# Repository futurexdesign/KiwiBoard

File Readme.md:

# Kiwiboard 
Control board for the KiwiCleaner watch cleaning machine.  Intended to provide an all-in-one option for the design. 

## Board Goals
- Have a single PCB with connections for the stepper motor, heater, fan, and user interface for ease of wiring. 
- Integrate a Trinamic silent stepper driver to greatly reduce volume. 
- Simplify the user interface for switching between run-modes. 
- Allow cooling fan to run for a timed period after a dry cycle, to allow the heater to safely cool down. 
- Not cost too much more than the original solution, with the understanding that there is greater functionality. 

## Theory of Operation
- Power input is 12V 
- Input is protected by a resettable PolyFuse with rated 10A constant load capacity.  
- Main Microcontroller is a RaspberryPi Pico (RP2040).  
  - This can be either the normal version, or the "header" version.  Can be mounted either way, board contains both the SMD and THT pads. 
- Display a 240x320 Color TFT LCD Connected via SPI
- User interface is controlled via a rotary encoder with pushbutton
- Pico has full control of stepper via SPI connection to the TMC5160 board. 
   - The Integrated Ramp Generator contained within the TMC5160 is utilized to control all motion, allowing very smooth and precise control over basket motion.  
- Pico can enable / disable the drive output via MOTOR_EN (Active Low)
- Pico can activate the Heater by pulling HEATER_CTL High, switching on the relay (3.3v coil).
- Pico can activate the fan by pulling FAN_CTL high, fan current conducted by the TIP120
- 3.3v power provided by a drop in switching powersupply module for simplicity. 
- All power connectors are Phoenix LPT lever connectors.  These support 12awg - 24awg up to a max of 24A.  Can substitute in SPT or any other phoenix connector with the same 5mm pin spacing

An expansion header has been added to support any additional mods people may want. *Example functionality would be a buzzer module to indicate end of cycle.*  Due to the flexability of the microcontroller, we can expose a ton of functionality on 4 pins.  The following IO is available on the expansion connector. 

- 4 independent GPIO pins for input/output 
- 1 hardware i2c bus (i2c1), and 2 GPIO pins (GPI0 and GPIO1)
- 4 pins with a PIO program assigned to them. 

Additionally the expansion header supplys 3.3V and GND connections.

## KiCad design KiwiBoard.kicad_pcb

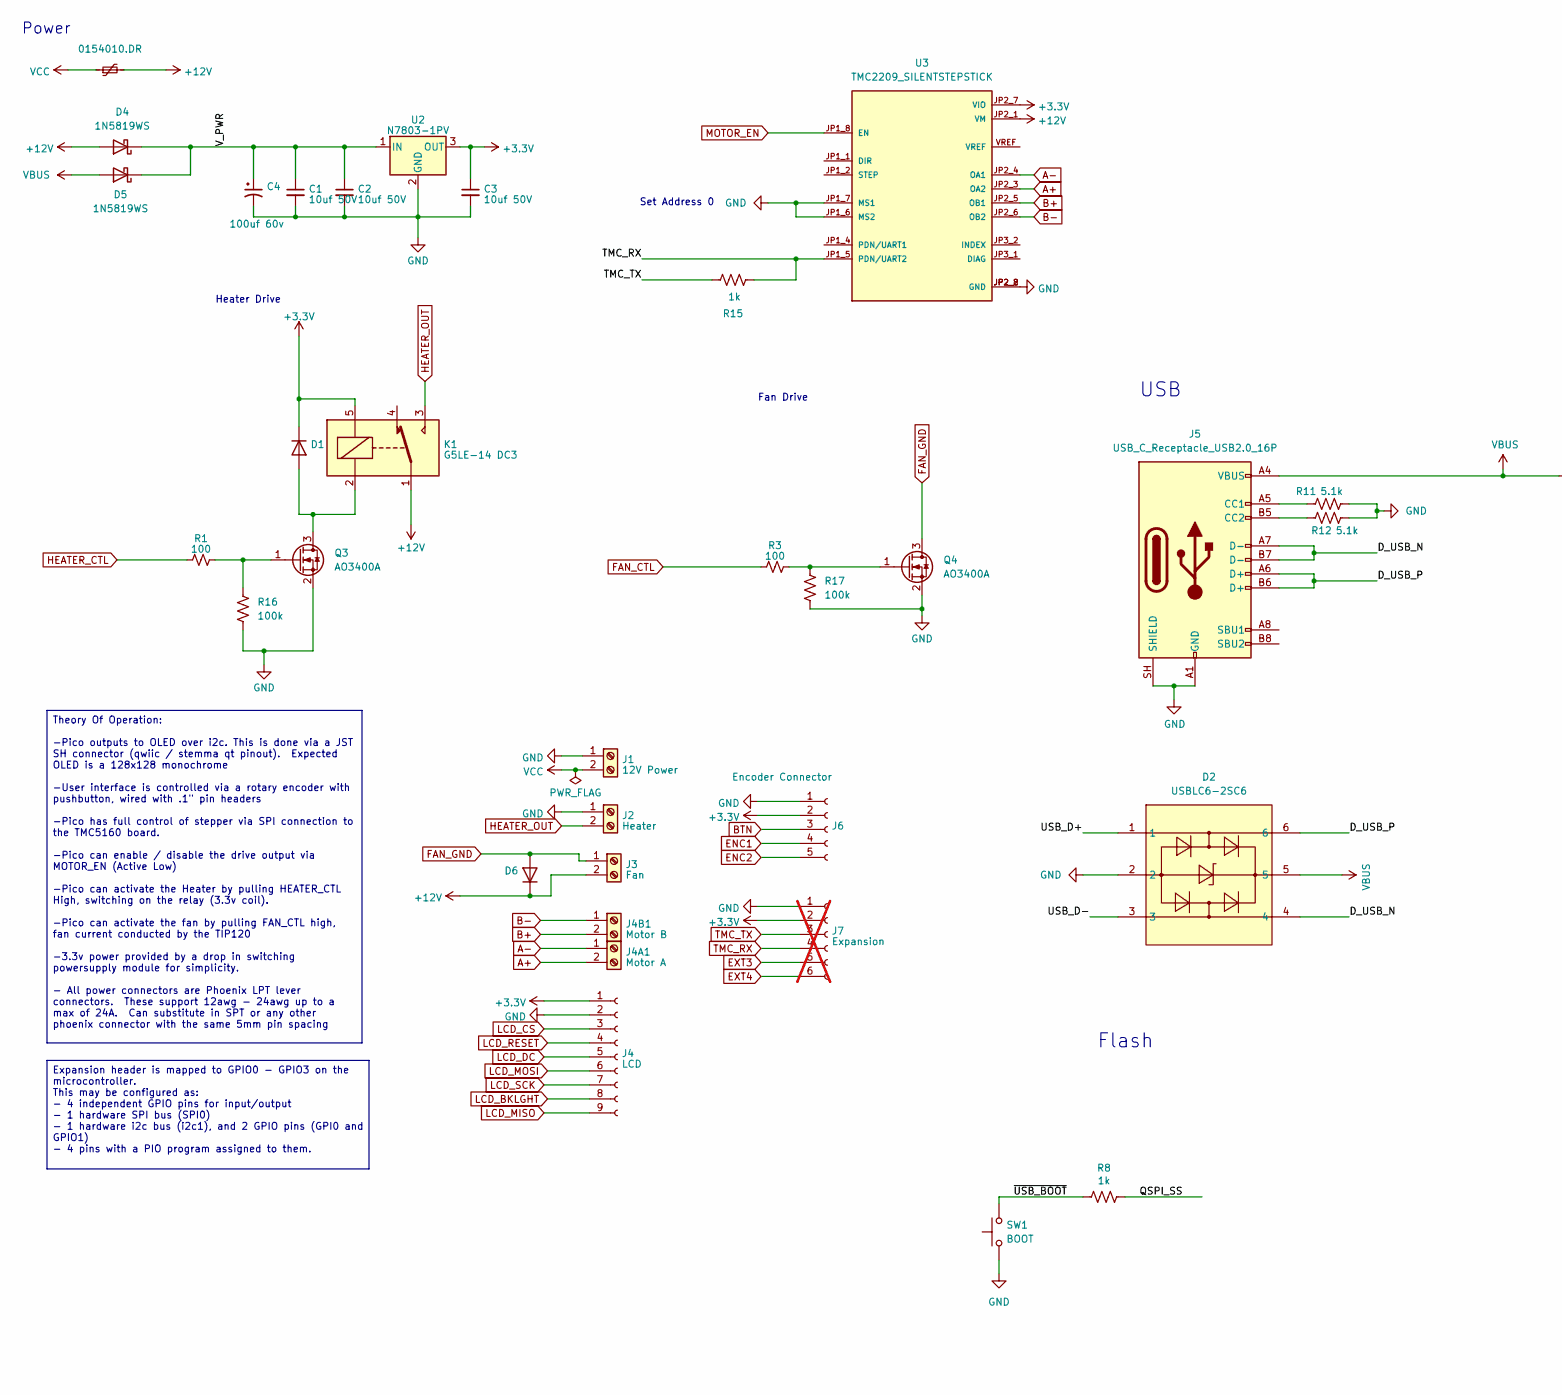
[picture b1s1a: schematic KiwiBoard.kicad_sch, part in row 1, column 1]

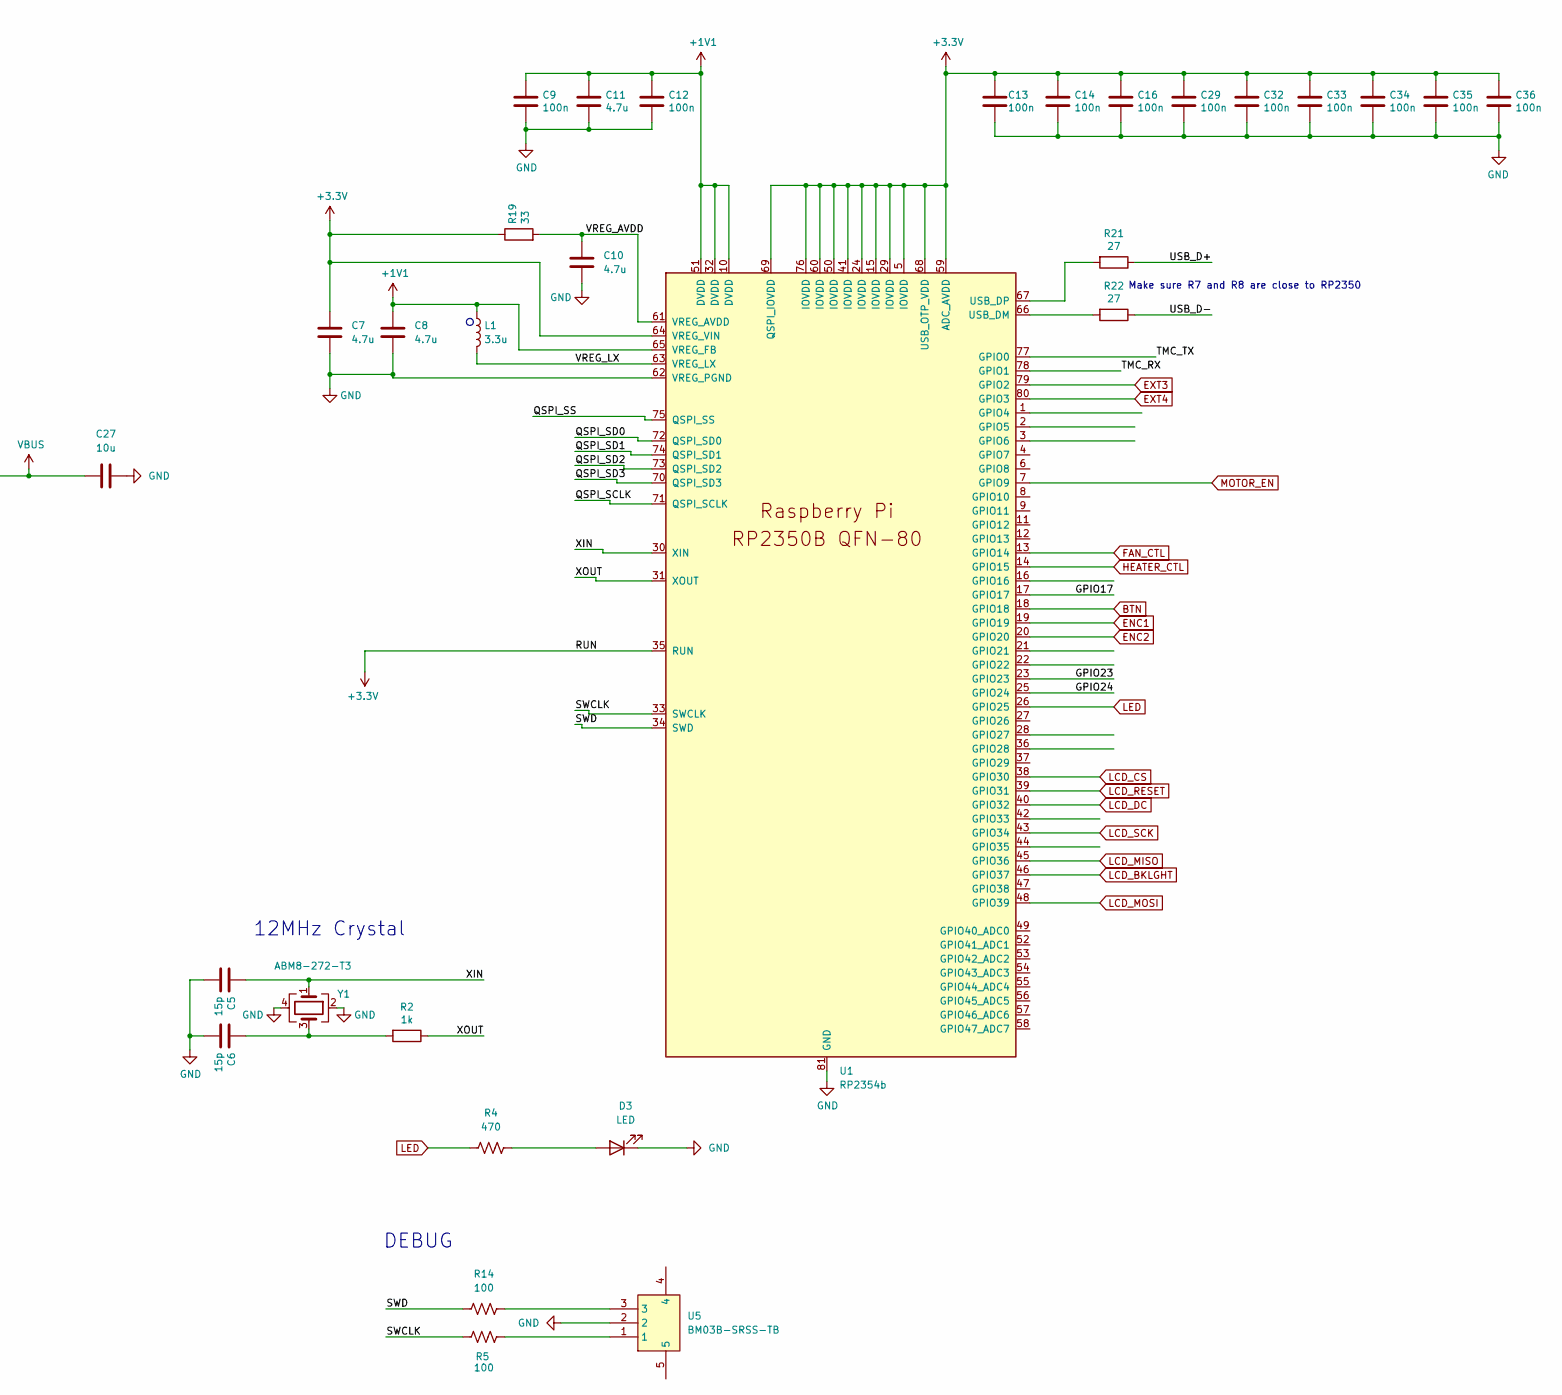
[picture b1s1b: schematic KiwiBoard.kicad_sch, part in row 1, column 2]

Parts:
C1, C2: 10uf 50V; C_1206_3216Metric; LCSC C13585
C3: 10uf 50V; C_1206_3216Metric; Partnumber CL31A106KBHNNNE; LCSC C13585
C4: 100uf 60v; CAP_EEFK_F_PAN; Part_Number EEEFP1H101AP; LCSC C401753
C5, C6: 15p; C_0402_1005Metric; LCSC C1548
C7, C8: 4.7u; C_0402_1005Metric_small_pads; LCSC C23733
C9, C12, C13, C14, C16, C29, C32, C33, C34, C35, C36: 100n; C_0402_1005Metric; LCSC C1525
C10, C11: 4.7u; C_0402_1005Metric; LCSC C23733
C27: 10u; C_0805_2012Metric; LCSC C15850
D1, D6: 1N4148WS; D_SOD-323; LCSC C2128
D2: USBLC6-2SC6; SOT-23-6; MPN USBLC6-2SC6; LCSC Part C7519
D3: LED; LED_0805_2012Metric; LCSC C84256
D4, D5: 1N5819WS; D_SOD-323; LCSC C191023
F1: 0154010.DR; FUSE-SMD_L9.7-W5.0; LCSC C206921
J1: 12V Power; CONN-TH_P5.00_KF2EDGV-5.0-2P; Part_Number 1190297; LCSC C441343
J2: Heater; CONN-TH_P5.00_KF2EDGV-5.0-2P; Part_Number 1190297; LCSC C441343
J3: Fan; CONN-TH_P5.00_KF2EDGV-5.0-2P; Part_Number 1190297; LCSC C441343
J4: LCD; JST_PH_B9B-PH-K_1x09_P2.00mm_Vertical; LCSC C157968
J4A1: Motor A; CONN-TH_P5.00_KF2EDGV-5.0-2P; Part_Number 1190297; LCSC C441343
J4B1: Motor B; CONN-TH_P5.00_KF2EDGV-5.0-2P; Part_Number 1190297; LCSC C441343
J5: USB_C_Receptacle_USB2.0_16P; USB_C_Receptacle_GCT_USB4105-xx-A_16P_TopMnt_Horizontal; LCSC C2765186
J6: Encoder Connector; JST_PH_B5B-PH-K_1x05_P2.00mm_Vertical; LCSC C157993
J7: Expansion; PinSocket_1x06_P2.54mm_Vertical; not fitted
K1: G5LE-14 DC3; Relay_SPDT_Omron-G5LE-1; LCSC C24585
L1: 3.3u; L_pol_2016; LCSC C42411119
Q3, Q4: AO3400A; SOT-23; LCSC C20917
R1, R3, R5, R14: 100; R_0402_1005Metric; LCSC C25076
R2, R8, R15: 1k; R_0402_1005Metric; LCSC C11702
R4: 470; R_0402_1005Metric; LCSC C25117
R11, R12: 5.1k; R_0603_1608Metric; LCSC C23186
R16, R17: 100k; R_0402_1005Metric; LCSC C25741
R19: 33; R_0402_1005Metric; LCSC C100382
R21, R22: 27; R_0402_1005Metric; LCSC C274349
SW1: BOOT; SW_SPST_SKQG_WithStem; LCSC C318884
U1: RP2354b; RP2350-QFN-80-1EP_10x10_P0.4mm_EP3.4x3.4mm_ThermalVias; LCSC C39843328
U2: N7803-1PV; Converter_DCDC_RECOM_R-78E-0.5_THT; LCSC C2916516
U3: TMC2209_SILENTSTEPSTICK; MODULE_TMC2208_SILENTSTEPSTICK
U5: BM03B-SRSS-TB; JST_SH_BM03B-SRSS-TB_1x03-1MP_P1.00mm_Vertical; MPN BM03B-SRSS-TB(LF)(SN); LCSC Part C160389
Y1: ABM8-272-T3; Crystal_SMD_3225-4Pin_3.2x2.5mm; LCSC C20625731

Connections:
+1V1: C8.1, C9.1, C11.1, C12.1, L1.1, U1.10 (DVDD), U1.32 (DVDD), U1.51 (DVDD), U1.65 (VREG_FB)
+3.3V: C3.1, C7.1, C13.1, C14.1, C16.1, C29.1, C32.1, C33.1, C34.1, C35.1, C36.1, D1.1 (K), J4.1, J6.2, J7.2, K1.5, R19.1, U1.5 (IOVDD), U1.15 (IOVDD), U1.24 (IOVDD), U1.29 (IOVDD), U1.35 (RUN), U1.41 (IOVDD), U1.50 (IOVDD), U1.59 (ADC_AVDD), U1.60 (IOVDD), U1.64 (VREG_VIN), U1.68 (USB_OTP_VDD), U1.69 (QSPI_IOVDD), U1.76 (IOVDD), U2.3 (OUT); also elsewhere on the board
+12V: D4.2 (A), D6.1 (K), F1.2, J3.2, K1.1, U3.JP2_1 (VM); also elsewhere on the board
/D_USB_N: D2.4, J5.A7 (D-), J5.B7 (D-)
/D_USB_P: D2.6, J5.A6 (D+), J5.B6 (D+)
/GPIO17: U1.17 (GPIO17)
/GPIO23: U1.23 (GPIO23)
/GPIO24: U1.25 (GPIO24)
/QSPI_SCLK: U1.71 (QSPI_SCLK)
/QSPI_SD0: U1.72 (QSPI_SD0)
/QSPI_SD1: U1.74 (QSPI_SD1)
/QSPI_SD2: U1.73 (QSPI_SD2)
/QSPI_SD3: U1.70 (QSPI_SD3)
/QSPI_SS: R8.1, U1.75 (QSPI_SS)
/SWCLK: R5.1, U1.33 (SWCLK)
/SWD: R14.1, U1.34 (SWD)
/USB_D+: D2.1, R21.1
/USB_D-: D2.3, R22.1
/VREG_AVDD: C10.1, R19.2, U1.61 (VREG_AVDD)
/VREG_LX: L1.2, U1.63 (VREG_LX)
/V_PWR: C1.1, C2.1, C4.1, D4.1 (K), D5.1 (K), U2.1 (IN)
/XIN: C5.1, U1.30 (XIN), Y1.1
/XOUT: R2.1, U1.31 (XOUT)
/~USB_BOOT: R8.2, SW1.2
A+: J4A1.2, U3.JP2_3 (OA2); also elsewhere on the board
A-: J4A1.1, U3.JP2_4 (OA1); also elsewhere on the board
B+: J4B1.2, U3.JP2_5 (OB1); also elsewhere on the board
B-: J4B1.1, U3.JP2_6 (OB2); also elsewhere on the board
BTN: J6.3, U1.18 (GPIO18)
ENC1: J6.4, U1.19 (GPIO19)
ENC2: J6.5, U1.20 (GPIO20)
EXT3: J7.5, U1.79 (GPIO2)
EXT4: J7.6, U1.80 (GPIO3)
FAN_CTL: R3.2, U1.13 (GPIO14)
FAN_GND: D6.2 (A), J3.1, Q4.3 (D)
GND: C1.2, C2.2, C3.2, C4.2, C5.2, C6.2, C7.2, C8.2, C9.2, C10.2, C11.2, C12.2, C13.2, C14.2, C16.2, C27.2, C29.2, C32.2, C33.2, C34.2, C35.2, C36.2, D2.2, D3.1 (K), J1.1, J2.1, J4.2, J5.A1 (GND), J5.A12 (GND), J5.B1 (GND), J5.B12 (GND), J5.SH (SHIELD), J6.1, J7.1, Q3.2 (S), Q4.2 (S), R11.2, R12.2, R16.1, R17.1, SW1.1, U1.62 (VREG_PGND), U1.81 (GND), U2.2 (GND), U5.2, Y1.2, Y1.4; also elsewhere on the board
HEATER_CTL: R1.2, U1.14 (GPIO15)
HEATER_OUT: J2.2, K1.3
LCD_BKLGHT: J4.8, U1.46 (GPIO37)
LCD_CS: J4.3, U1.38 (GPIO30)
LCD_DC: J4.5, U1.40 (GPIO32)
LCD_MISO: J4.9, U1.45 (GPIO36)
LCD_MOSI: J4.6, U1.48 (GPIO39)
LCD_RESET: J4.4, U1.39 (GPIO31)
LCD_SCK: J4.7, U1.43 (GPIO34)
LED: R4.1, U1.26 (GPIO25)
MOTOR_EN: U1.7 (GPIO9), U3.JP1_8 (EN); also elsewhere on the board
unnamed: C6.1, R2.2, Y1.3
unnamed: D1.2 (A), K1.2, Q3.3 (D)
unnamed: D3.2 (A), R4.2
unnamed: J5.A5 (CC1), R11.1
unnamed: J5.B5 (CC2), R12.1
unnamed: Q3.1 (G), R1.1, R16.2
unnamed: Q4.1 (G), R3.1, R17.2
unnamed: R5.2, U5.1
unnamed: R14.2, U5.3
unnamed: R22.2, U1.66 (USB_DM)
unnamed: R21.2, U1.67 (USB_DP)
TMC_RX: J7.4, R15.2, U1.78 (GPIO1), U3.JP1_5 (PDN/UART2); also elsewhere on the board
TMC_TX: J7.3, R15.1, U1.77 (GPIO0)
VBUS: C27.1, D2.5, D5.2 (A), J5.A4 (VBUS), J5.A9 (VBUS), J5.B4 (VBUS), J5.B9 (VBUS)
VCC: F1.1, J1.2

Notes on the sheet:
Make sure R7 and R8 are close to RP2350
Heater Drive
Fan Drive
USB
12MHz Crystal
Flash
Set Address 0
Power
DEBUG
Expansion header is mapped to GPIO0 - GPIO3 on the microcontroller. This may be configured as: - 4 independent GPIO pins for input/output - 1 hardware SPI bus (SPI0) - 1 hardware i2c bus (i2c1), and 2 GPIO pins (GPI0 and GPIO1) - 4 pins with a PIO program assigned to them.
Theory Of Operation: -Pico outputs to OLED over i2c. This is done via a JST SH connector (qwiic / stemma qt pinout). Expected OLED is a 128x128 monochrome -User interface is controlled via a rotary encoder with pushbutton, wired with .1" pin headers -Pico has full control of stepper via SPI connect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

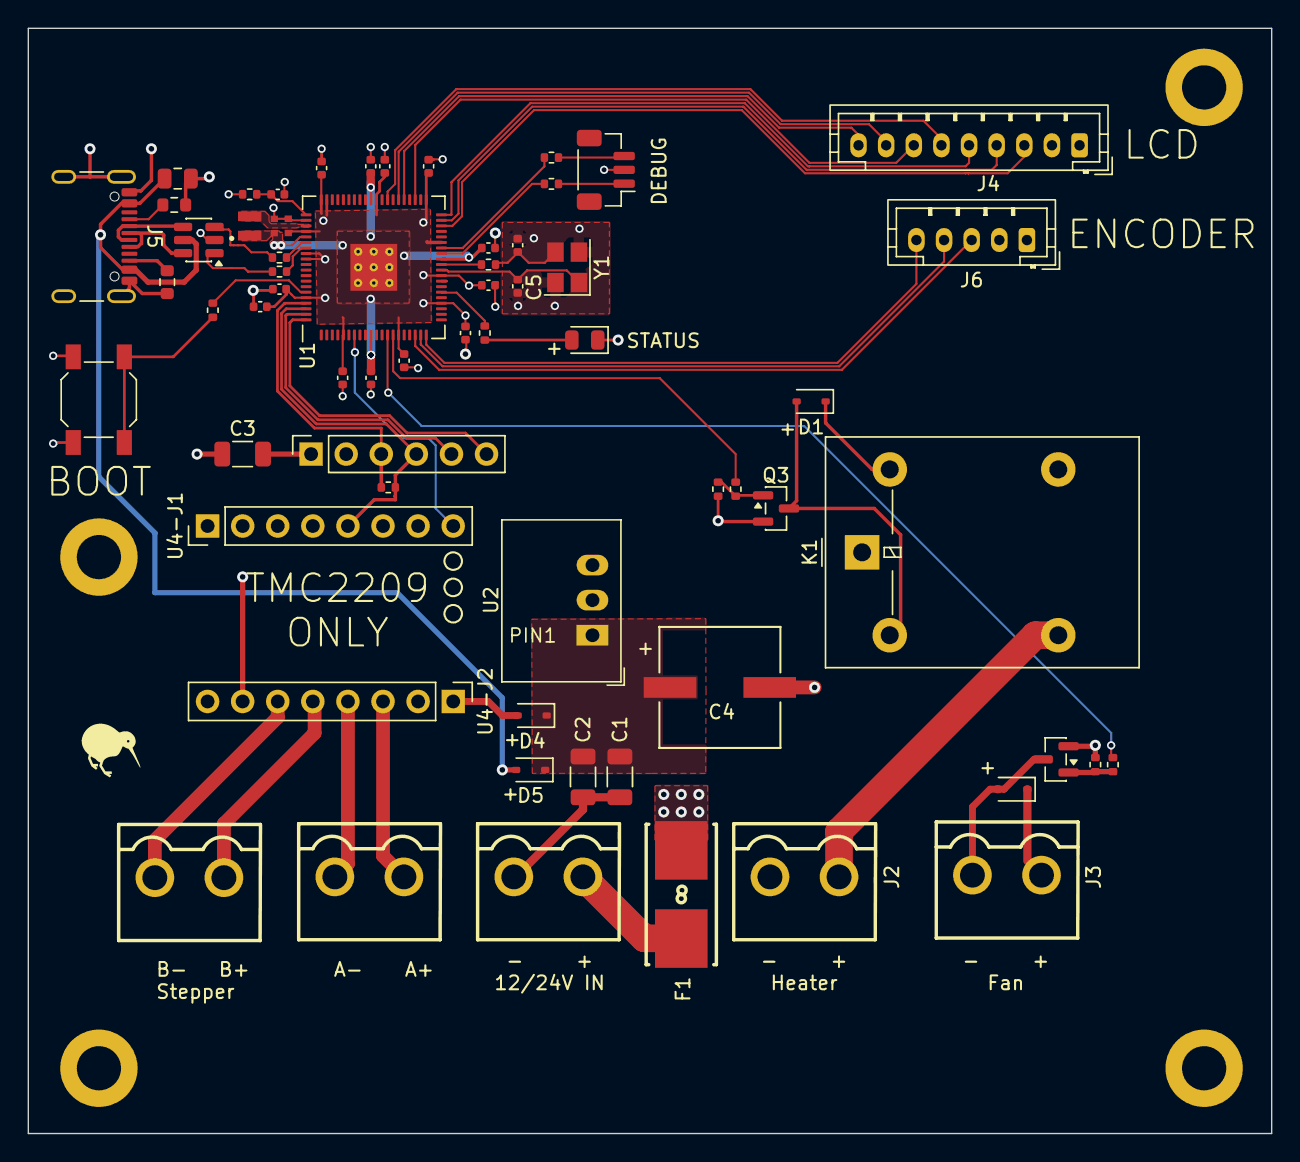
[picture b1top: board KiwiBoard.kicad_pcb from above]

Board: 4 copper layers, 90.0 x 80.0 mm, 64 parts (0 on the bottom side), 54 nets.

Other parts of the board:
U4-J1, U4-J2: PinHeader_1x08_P2.54mm_Vertical

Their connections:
+3.3V: U4-J2.7; also elsewhere on the board
+12V: U4-J2.1; also elsewhere on the board
A+: U4-J2.3; also elsewhere on the board
A-: U4-J2.4; also elsewhere on the board
B+: U4-J2.5; also elsewhere on the board
B-: U4-J2.6; also elsewhere on the board
GND: U4-J1.6, U4-J1.7, U4-J2.2, U4-J2.8; also elsewhere on the board
MOTOR_EN: U4-J1.8; also elsewhere on the board
TMC_RX: U4-J1.5; also elsewhere on the board

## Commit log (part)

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2023-04-01 Initial
2023-04-01 Readme
2023-04-04 Mechanical layout with original connectors
2023-04-06 Change to JST PH connectors for OLED and Encoder. Adjust spacing for the 3v3 regulator
2023-04-07 Change to 2p connectors for the motor. Retaining the ability to use the 2row connectors or one row connectors
2023-04-09 reworked with JST PH connectors, move raspi to board edge
2023-04-11 Rev2 board, LCD connector, adjusted Q1 footprint. Pico slid to edge
2023-04-13 Create License
2023-12-24 resize upper row of holes, add a bird
2025-10-26 Rev4
2026-06-27 Switch to TMC2209 Embed RP2040 Switch to USB C Add debug SWD connector 4 layer board
